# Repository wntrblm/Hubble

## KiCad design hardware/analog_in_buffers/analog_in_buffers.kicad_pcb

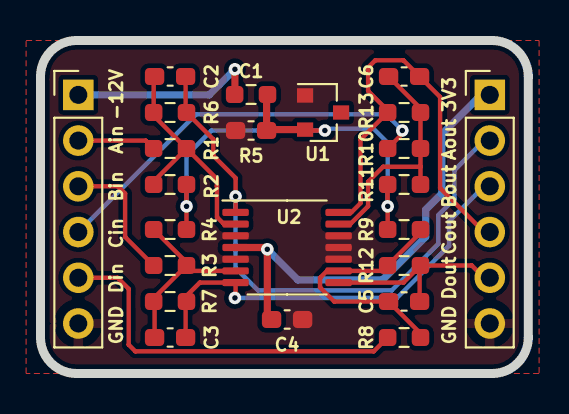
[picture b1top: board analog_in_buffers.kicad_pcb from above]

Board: 2 copper layers, 27.1 x 18.5 mm, 23 parts (0 on the bottom side), 16 nets.

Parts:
C1, C4: 0.1uF; C_0603_1608Metric_Pad1.08x0.95mm_HandSolder
C2, C3, C5, C6: 22pF; C_0603_1608Metric_Pad1.08x0.95mm_HandSolder
J1: INPUT; PinHeader_1x06_P2.54mm_Vertical
J2: OUTPUT; PinHeader_1x06_P2.54mm_Vertical
R1, R3, R8, R10: 100k; R_0603_1608Metric_Pad0.98x0.95mm_HandSolder
R2, R4, R9, R11: 121k; R_0603_1608Metric_Pad0.98x0.95mm_HandSolder
R5: 1k; R_0603_1608Metric_Pad0.98x0.95mm_HandSolder
R6, R7, R12, R13: 18.7k; R_0603_1608Metric_Pad0.98x0.95mm_HandSolder
U1: LM4040-10; SOT-23
U2: MCP6004; TSSOP-14_4.4x5mm_P0.65mm

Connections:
+3V3: C4.1, J2.1, U2.4
-10V: C1.2, R2.2, R4.2, R5.1, R9.2, R11.2, U1.2
-12V: J1.1, R5.2
/IN_A: J1.2, R1.2
/IN_B: J1.3, R3.2
/IN_C: J1.4, R10.2
/IN_D: J1.5, R8.2
/OUT_A: C2.2, J2.2, R6.1, U2.1
/OUT_B: C3.2, J2.3, R7.1, U2.7
/OUT_C: C6.2, J2.4, R13.1, U2.14
/OUT_D: C5.2, J2.5, R12.1, U2.8
GND: C1.1, C4.2, J1.6, J2.6, U1.1, U2.3, U2.5, U2.10, U2.11, U2.12
unnamed: C2.1, R1.1, R2.1, R6.2, U2.2
unnamed: C3.1, R3.1, R4.1, R7.2, U2.6
unnamed: C5.1, R8.1, R9.1, R12.2, U2.9
unnamed: C6.1, R10.1, R11.1, R13.2, U2.13

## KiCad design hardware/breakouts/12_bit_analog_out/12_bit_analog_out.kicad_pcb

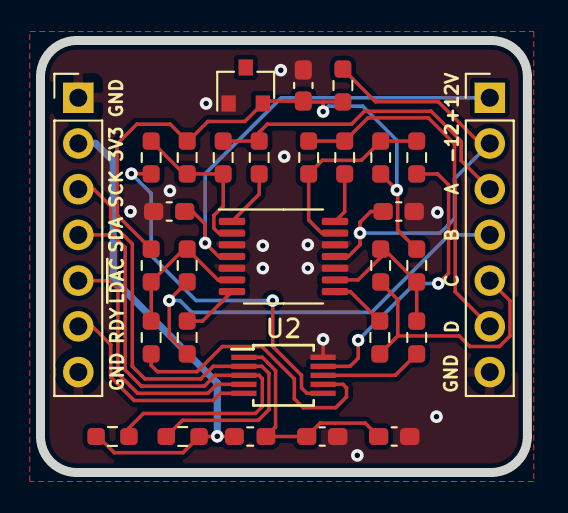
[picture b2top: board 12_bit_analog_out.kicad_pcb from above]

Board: 2 copper layers, 27.1 x 24.0 mm, 30 parts (0 on the bottom side), 26 nets.

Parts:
C1: 1uF; C_0603_1608Metric_Pad1.08x0.95mm_HandSolder
C2, C4, C5, C6: 0.1uF; C_0603_1608Metric_Pad1.08x0.95mm_HandSolder
FB1: BEAD; L_0603_1608Metric_Pad1.05x0.95mm_HandSolder
J1: Inputs; PinHeader_1x07_P2.54mm_Vertical
J2: Outputs; PinHeader_1x07_P2.54mm_Vertical
R1: 270; R_0603_1608Metric_Pad0.98x0.95mm_HandSolder
R2, R4, R6, R8: 1.54k; R_0603_1608Metric_Pad0.98x0.95mm_HandSolder
R3, R5, R7, R9: 12.4k; R_0603_1608Metric_Pad0.98x0.95mm_HandSolder
R10, R11, R12, R13, R18, R19: 10k; R_0603_1608Metric_Pad0.98x0.95mm_HandSolder
R14, R15, R16, R17: 1k; R_0603_1608Metric_Pad0.98x0.95mm_HandSolder
U1: LM4040-10; SOT-23
U2: MCP4728; MSOP-10_3x3mm_P0.5mm
U3: OPA4197; TSSOP-14_4.4x5mm_P0.65mm

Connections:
+3.3VA: C1.2, C2.2, FB1.1, U2.1
+3V3: FB1.2, J1.2, R18.2, R19.2
+12V: C5.2, J2.1, U3.4
-10V: C4.2, R1.1, R3.2, R5.2, R7.2, R9.2, U1.2
-12V: C6.2, J2.2, R1.2, U3.11
/DAC_OUT_A: R2.2, U2.6
/DAC_OUT_B: R4.2, U2.7
/DAC_OUT_C: R6.2, U2.8
/DAC_OUT_D: R8.2, U2.9
/OUT_A: J2.3, R10.1, R14.1
/OUT_B: J2.4, R11.1, R15.1
/OUT_C: J2.5, R12.1, R16.1
/OUT_D: J2.6, R13.1, R17.1
/RDY: J1.6, U2.5
/SCL: J1.3, R18.1, U2.2
/SDA: J1.4, R19.1, U2.3
/~LDAC: J1.5, U2.4
GND: C1.1, C2.1, C4.1, C5.1, C6.1, J1.1, J1.7, J2.7, U1.1, U2.10, U3.3, U3.5, U3.10, U3.12
unnamed: R2.1, R3.1, R10.2, U3.2
unnamed: R4.1, R5.1, R11.2, U3.6
unnamed: R6.1, R7.1, R12.2, U3.9
unnamed: R8.1, R9.1, R13.2, U3.13
unnamed: R14.2, U3.1
unnamed: R15.2, U3.7
unnamed: R16.2, U3.8
unnamed: R17.2, U3.14

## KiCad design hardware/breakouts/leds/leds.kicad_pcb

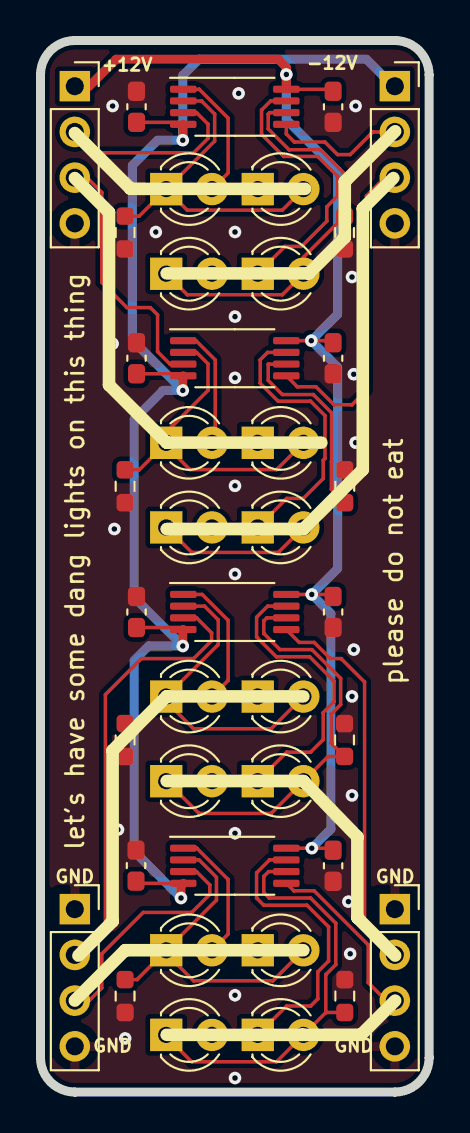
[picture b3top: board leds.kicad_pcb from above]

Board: 2 copper layers, 21.6 x 58.4 mm, 40 parts (0 on the bottom side), 27 nets.

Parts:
C1, C2, C3, C4, C5, C6, C7, C8: 0.1uF; C_0603_1608Metric_Pad1.08x0.95mm_HandSolder
D1, D2, D5, D6, D9, D10, D13, D14: POS; LED_D3.0mm
D3, D4, D7, D8, D11, D12, D15, D16: NEG; LED_D3.0mm
J3: L1; PinSocket_1x04_P2.54mm_Vertical
J4: L2; PinSocket_1x04_P2.54mm_Vertical
J5: R1; PinSocket_1x04_P2.54mm_Vertical
J6: R2; PinSocket_1x04_P2.54mm_Vertical
R1, R2, R3, R4, R5, R6, R7, R8: 1k; R_0603_1608Metric_Pad0.98x0.95mm_HandSolder
U1, U2, U3, U4: LM358; TSSOP-8_4.4x3mm_P0.65mm

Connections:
+12V: C2.1, C4.1, C7.1, C8.1, J3.1, U1.8, U2.8, U3.8, U4.8
-12V: C1.1, C3.1, C5.1, C6.1, J5.1, U1.4, U2.4, U3.4, U4.4
/IN1: J3.2, U1.3
/IN2: J5.2, U1.5
/IN3: J3.3, U2.3
/IN4: J5.3, U2.5
/IN5: J4.2, U3.3
/IN6: J6.2, U3.5
/IN7: J4.3, U4.3
/IN8: J6.3, U4.5
GND: C1.2, C2.2, C3.2, C4.2, C5.2, C6.2, C7.2, C8.2, J3.4, J4.1, J4.4, J5.4, J6.1, J6.4, R1.2, R2.2, R3.2, R4.2, R5.2, R6.2, R7.2, R8.2
unnamed: D1.1, D3.2, R1.1, U1.2
unnamed: D1.2, D3.1, U1.1
unnamed: D2.1, D4.2, R2.1, U1.6
unnamed: D2.2, D4.1, U1.7
unnamed: D5.1, D7.2, R3.1, U2.2
unnamed: D5.2, D7.1, U2.1
unnamed: D6.1, D8.2, R4.1, U2.6
unnamed: D6.2, D8.1, U2.7
unnamed: D10.1, D12.2, R6.1, U3.6
unnamed: D10.2, D12.1, U3.7
unnamed: D9.2, D11.1, U3.1
unnamed: D9.1, D11.2, R5.1, U3.2
unnamed: D13.1, D15.2, R7.1, U4.2
unnamed: D13.2, D15.1, U4.1
unnamed: D14.1, D16.2, R8.1, U4.6
unnamed: D14.2, D16.1, U4.7

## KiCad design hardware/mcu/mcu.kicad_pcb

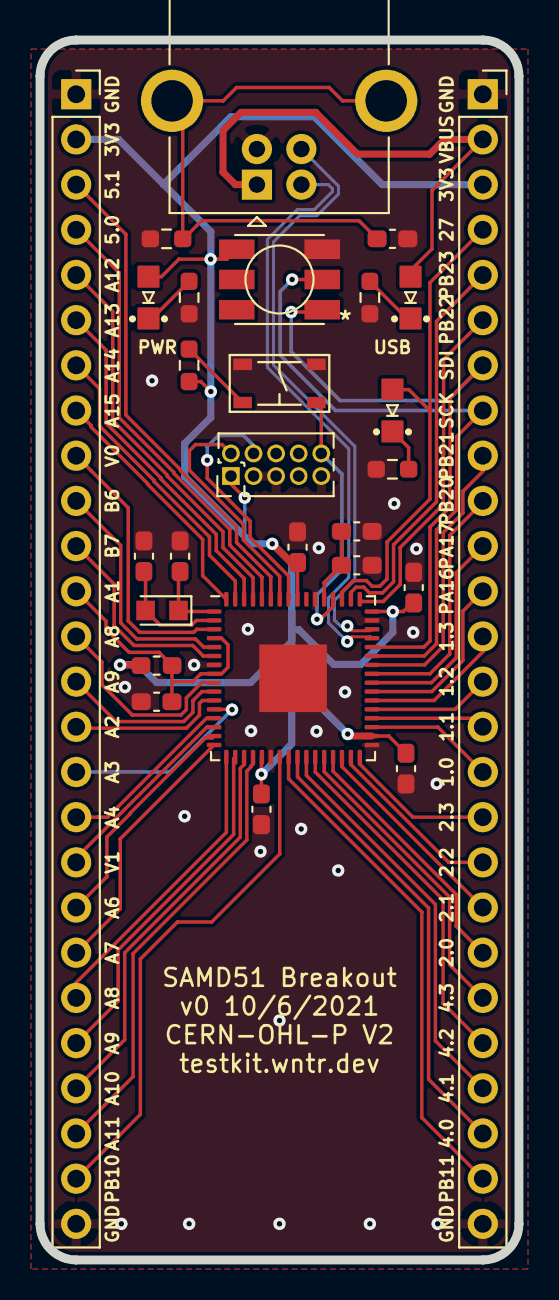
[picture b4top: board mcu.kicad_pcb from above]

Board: 2 copper layers, 26.9 x 68.6 mm, 27 parts (0 on the bottom side), 60 nets.

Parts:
C1, C2: 18pF; C_0603_1608Metric_Pad1.08x0.95mm_HandSolder
C3: 4.7nF; C_0603_1608Metric_Pad1.08x0.95mm_HandSolder
C4, C5, C7, C8, C9, C10: 0.1uF; C_0603_1608Metric_Pad1.08x0.95mm_HandSolder
C6: 4.7uF; C_0603_1608Metric_Pad1.08x0.95mm_HandSolder
D1: POWER; LED_0805_Kingbright_APT2012
D2: USB; LED_0805_Kingbright_APT2012
D3: Dotstar; Dotstar_5050
D4: ACT; LED_0805_Kingbright_APT2012
FB1: 300mA; L_0603_1608Metric_Pad1.05x0.95mm_HandSolder
J1: USB_B_Receptacle; USB_B_OST_USB-B1HSxx_Horizontal
J2: SWD; PinHeader_2x05_P1.27mm_Vertical
J3, J4: Conn_01x26; PinSocket_1x26_P2.54mm_Vertical
R1, R2, R3, R4, R5: 10k; R_0603_1608Metric_Pad0.98x0.95mm_HandSolder
SW1: RESET; Tactile_Switch_4.2mm
U2: ATSAMD51J20A-M; QFN-64-1EP_9x9mm_P0.5mm_EP3.8x3.8mm
Y1: 32.768kHz; Crystal_SMD_2012-2Pin_2.0x1.2mm_HandSoldering

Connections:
+3V3: C7.1, C8.1, C9.1, C10.1, D1.2, D3.4, FB1.2, J2.1, J3.2, J4.3, R3.1, U2.21, U2.34, U2.48, U2.56
/ADC0.AIN1+ANAREF.VREF0: C4.1, FB1.1, J3.12, U2.4, U2.8
/ADC0.AIN2+ADC1.AIN0: J3.15, U2.11
/ADC0.AIN3+ADC1.AIN1: J3.16, U2.12
/ADC0.AIN4+ANAREF.VREF1: J3.17, U2.13
/ADC0.AIN6+ANAREF.VREF2: J3.19, U2.15
/ADC0.AIN7: J3.20, U2.16
/ADC0.AIN8+ADC1.AIN2: J3.21, U2.17
/ADC0.AIN9+ADC1.AIN3: J3.22, U2.18
/ADC0.AIN10: J3.23, U2.19
/ADC0.AIN11: J3.24, U2.20
/ADC0.AIN12: J3.5, U2.61
/ADC0.AIN13: J3.6, U2.62
/ADC0.AIN14: J3.7, U2.63
/ADC0.AIN15: J3.8, U2.64
/ADC1.AIN6: J3.10, U2.5
/ADC1.AIN7: J3.11, U2.6
/ADC1.AIN8: J3.13, U2.9
/ADC1.AIN9: J3.14, U2.10
/D+: J1.3, U2.46
/D-: J1.2, U2.45
/DAC.VOUT0: J3.9, U2.3
/DAC.VOUT1: J3.18, U2.14
/DOTSTAR_SCK: D3.2, J4.8, U2.43
/DOTSTAR_SDI: D3.1, J4.7, U2.44
/PA16: J4.12, U2.39
/PA17: J4.11, U2.40
/PA20: J4.10, U2.41
/PA21: J4.9, U2.42
/PA27: D4.2, J4.4, U2.51
/PB10: J3.25, U2.23
/PB11: J4.25, U2.24
/PB22: J4.6, U2.49
/PB23: J4.5, U2.50
/RESET: J2.10, R3.2, SW1.1, U2.52
/SERCOM1.0: J4.16, U2.35
/SERCOM1.1: J4.15, U2.36
/SERCOM1.2: J4.14, U2.37
/SERCOM1.3: J4.13, U2.38
/SERCOM2.0: J4.20, U2.29
/SERCOM2.1: J4.19, U2.30
/SERCOM2.2: J4.18, U2.31
/SERCOM2.3: J4.17, U2.32
/SERCOM4.0: J4.24, U2.25
/SERCOM4.1: J4.23, U2.26
/SERCOM4.2: J4.22, U2.27
/SERCOM4.3: J4.21, U2.28
/SERCOM5.0: J3.4, U2.60
/SERCOM5.1: J3.3, U2.59
/SWCLK: J2.4, U2.57
/SWDIO: J2.2, U2.58
/VBUS: D2.2, J1.1, J4.2
/VDDCORE: C5.1, C6.1, U2.53
/XIN: C1.1, U2.1, Y1.1
/XOUT: C2.1, U2.2, Y1.2
GND: C1.2, C2.2, C3.2, C4.2, C5.2, C6.2, C7.2, C8.2, C9.2, C10.2, D3.3, J1.4, J2.3, J2.5, J2.9, J3.1, J3.26, J4.1, J4.26, R1.2, R2.2, R4.2, R5.2, SW1.2, U2.7, U2.22, U2.33, U2.47, U2.54, U2.65
unnamed: C3.1, J1.5, R4.1
unnamed: D1.1, R1.1
unnamed: D2.1, R2.1
unnamed: D4.1, R5.1

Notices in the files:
hardware/analog_in_buffers/analog_in_buffers.kicad_pcb:
CERN OHL-P V2
